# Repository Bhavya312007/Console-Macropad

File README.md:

# Console-Macropad

Bat-Board is a 10 key macropad with an OLED Display. It uses QMK firmware, easy to use and customize macro

I tried to make a multipupose and multi layer macropad. 1 layer for 1 purpose. It will work like them but need a better case more like acrylic. I have used all of this first time. It was fun somtimes and sometimes frustrating. If think i need to add a stand like system in the case but building it is a liitle hard for me.

## Features:
- Multilayer Functionality.
- 128x32 OLED Display
- First key for main controller or for whatever you want
- 10 Keys

## PCB
Here's my PCB! It was made in KiCad. I was thing of using a silkscreen but didn't like anything .

Schematic
- [Schematics](/PCB/Macropad_Schematics.pdf) 

## Firmware Overview
This hackpad uses [QMK](https://qmk.fm/) firmware for everything. 

- The main left button is for contol purpose works as togle and to switch between layers and more. More like ctrl button of keyboard
- Last 4 white keys will be the arrow keys of keyboard. Other keys are custom set macros and links.
- The OLED is Not decided yet but i am thing of something from naruto or demon slayer

I might add more in the future! That's it for now

## CAD:

## BOM:

Here should be everything you need to make this hackpad

- 13x Cherry MX Switches
- 4x SK6812 MINI Leds
- 1x XIAO RP2040
- 4x Blank DSA Keycaps
- 9x M3x16 Bolt
- 9x M3 Heatset
- 1x 0.91" 128x32 OLED Display
- 13x Through-hole 1N4148 Diodes
- 1x Red Blank DSA keycaps
- 4x White Blank DSA keycaps
- 9x Black Blank DSA keycaps
- 9x M3 hex nuts

Extras:-
- Few Jump Wires
- Breadboard
- A soldering iron and its required materials
For testing before placing
- a sd card

Others:
- KMK Firmware
- Top Case.stl 
- Bottom Case.stl

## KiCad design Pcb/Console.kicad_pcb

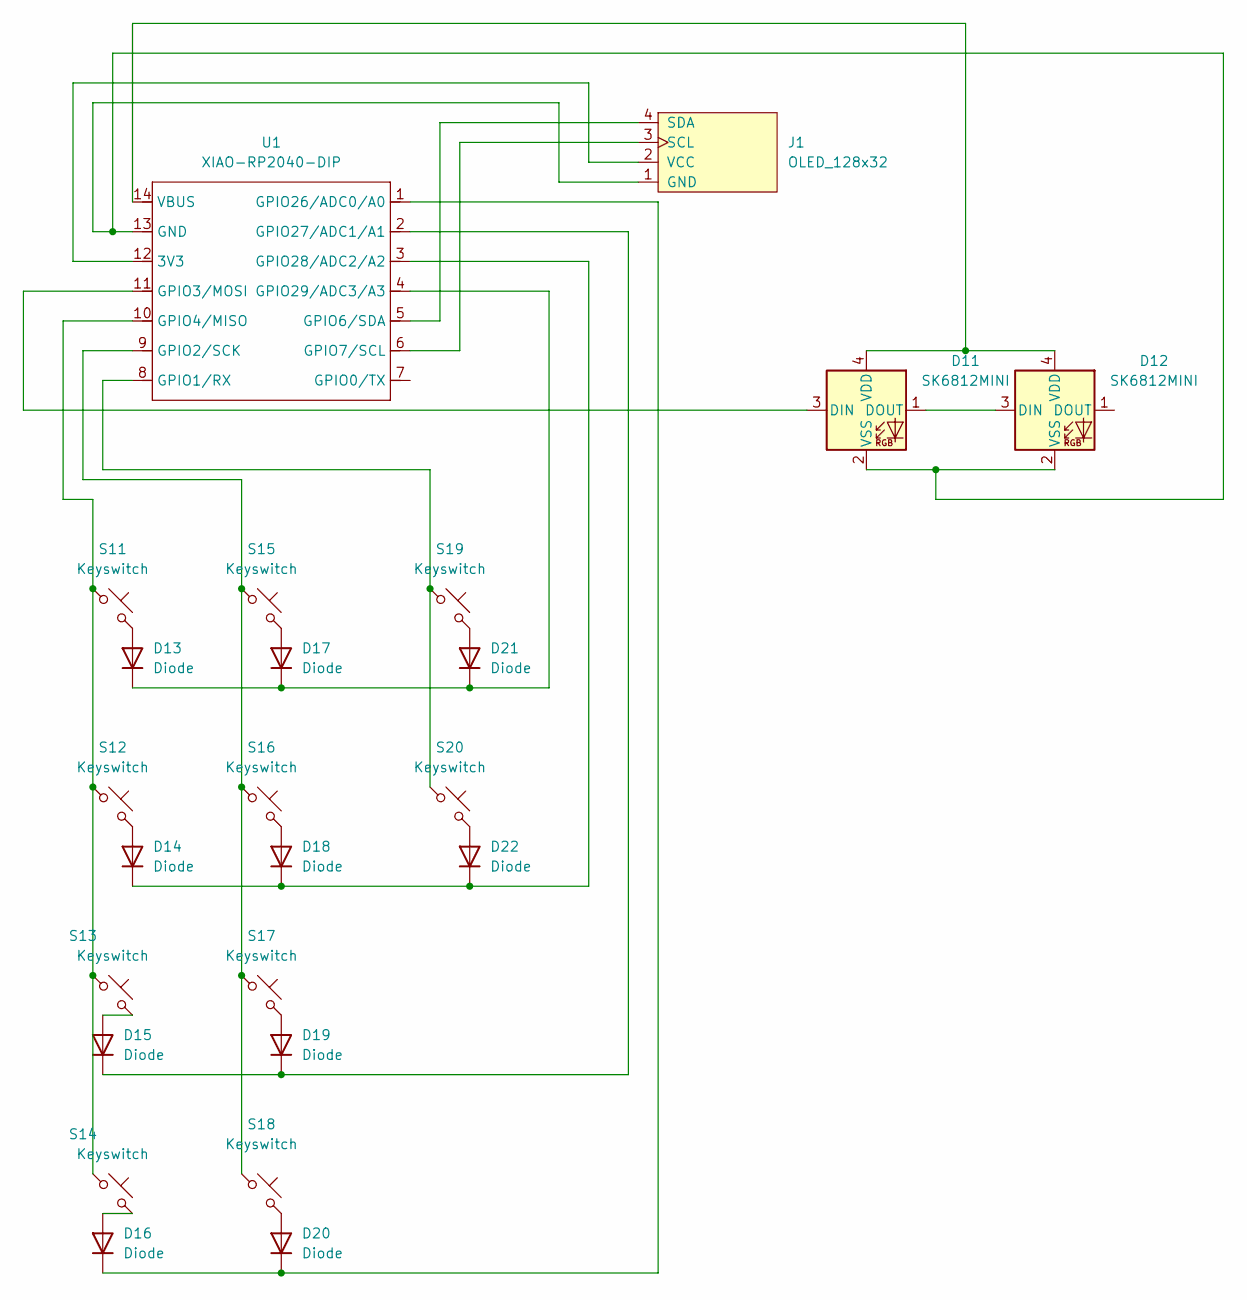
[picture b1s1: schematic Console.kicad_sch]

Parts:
D11, D12: SK6812MINI; LED_SK6812MINI_PLCC4_3.5x3.5mm_P1.75mm
D13, D14, D15, D16, D17, D18, D19, D20, D21, D22: Diode; Diode_DO-35
J1: OLED_128x32
S11, S12, S13, S14, S15, S16, S17, S18, S19, S20: Keyswitch; SW_Cherry_MX_1.00u_PCB
U1: XIAO-RP2040-DIP

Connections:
unnamed: D11.3 (DIN), U1.11 (GPIO3/MOSI)
unnamed: D11.1 (DOUT), D12.3 (DIN)
unnamed: D11.4 (VDD), D12.4 (VDD), U1.14 (VBUS)
unnamed: D11.2 (VSS), D12.2 (VSS), J1.1 (GND), U1.13 (GND)
unnamed: D13.2 (A), S11.2
unnamed: D13.1 (K), D17.1 (K), D21.1 (K), U1.4 (GPIO29/ADC3/A3)
unnamed: D14.2 (A), S12.2
unnamed: D14.1 (K), D18.1 (K), D22.1 (K), U1.3 (GPIO28/ADC2/A2)
unnamed: D15.2 (A), S13.2
unnamed: D15.1 (K), D19.1 (K), U1.2 (GPIO27/ADC1/A1)
unnamed: D16.2 (A), S14.2
unnamed: D16.1 (K), D20.1 (K), U1.1 (GPIO26/ADC0/A0)
unnamed: D17.2 (A), S15.2
unnamed: D18.2 (A), S16.2
unnamed: D19.2 (A), S17.2
unnamed: D20.2 (A), S18.2
unnamed: D21.2 (A), S19.2
unnamed: D22.2 (A), S20.2
unnamed: J1.3 (SCL), U1.6 (GPIO7/SCL)
unnamed: J1.4 (SDA), U1.5 (GPIO6/SDA)
unnamed: J1.2 (VCC), U1.12 (3V3)
unnamed: S19.1, S20.1, U1.8 (GPIO1/RX)
unnamed: S15.1, S16.1, S17.1, S18.1, U1.9 (GPIO2/SCK)
unnamed: S11.1, S12.1, S13.1, S14.1, U1.10 (GPIO4/MISO)

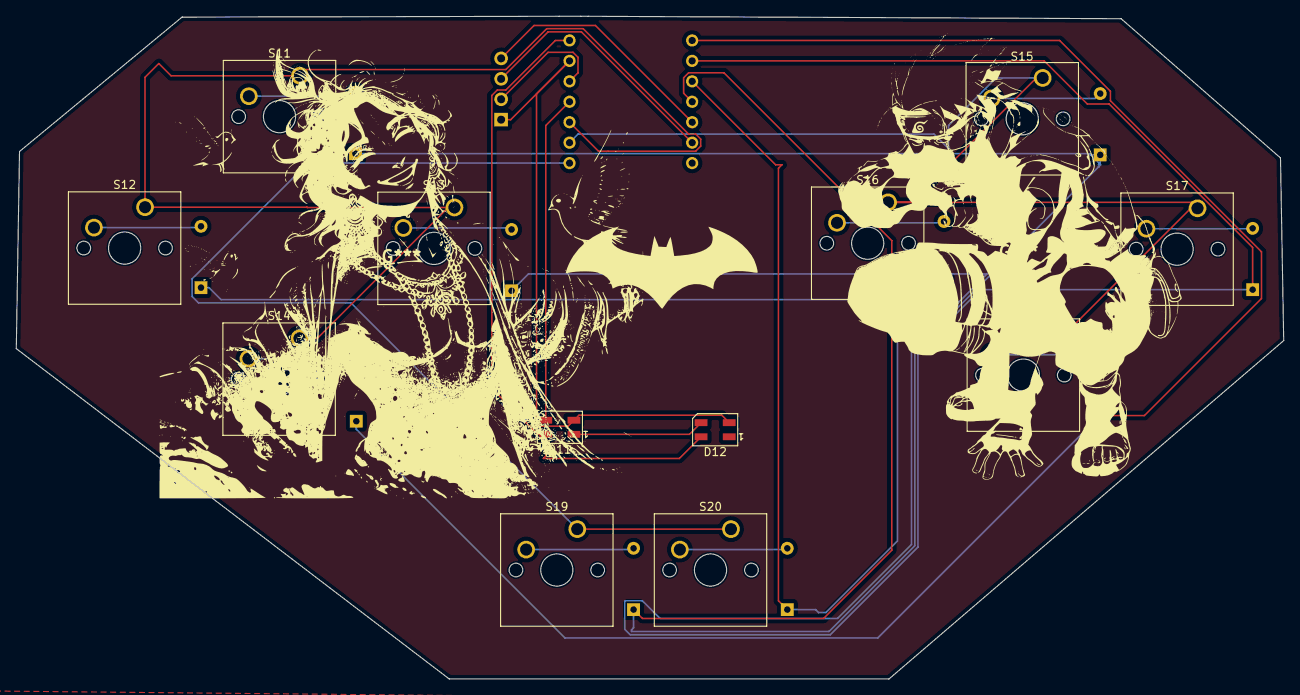
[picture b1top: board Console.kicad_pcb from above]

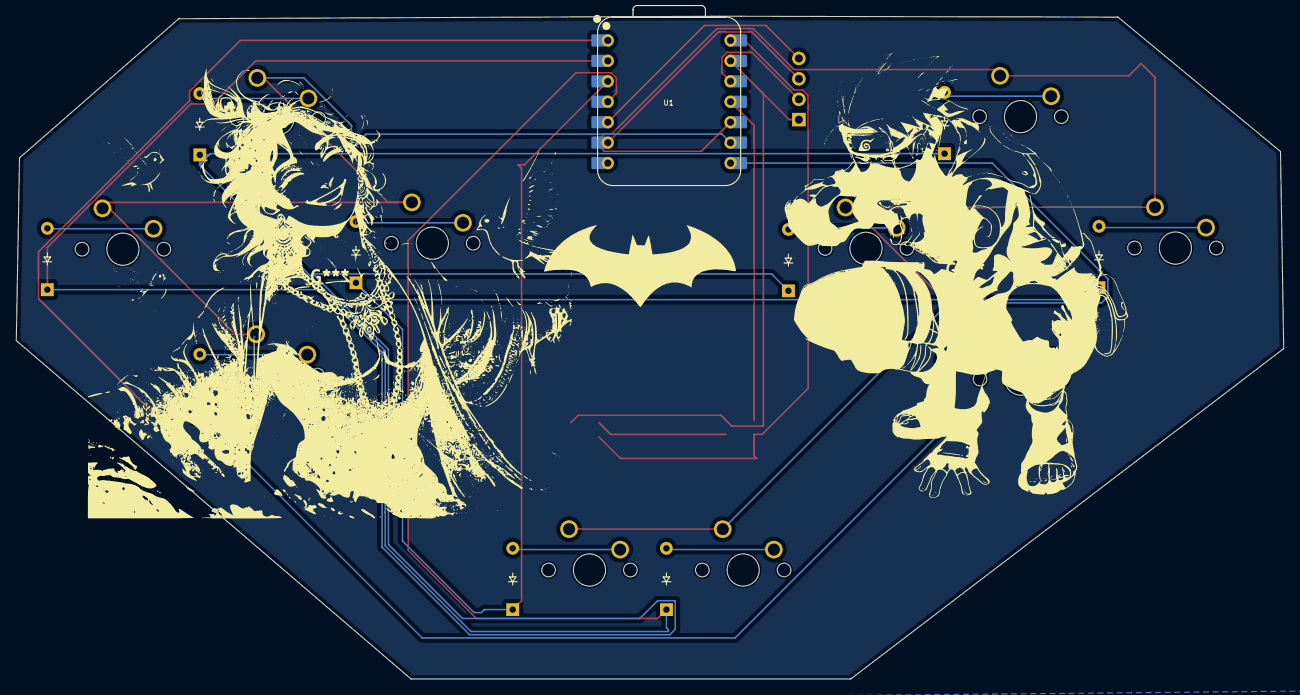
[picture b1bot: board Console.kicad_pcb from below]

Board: 2 copper layers, 157.5 x 82.4 mm, 24 parts (11 on the bottom side), 24 nets.

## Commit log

2025-02-18 Imported cad files
